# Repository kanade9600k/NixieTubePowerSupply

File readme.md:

# NixieTubePowerSupply

## 概要

* ニキシー管用の高電圧と制御用の電圧を生成する電源回路基板
* デフォルトでは200Vと5Vを生成
* 5Vだけとしても利用可能
* パーツを変えることで他の電圧ようにも流用可

## 回路図

## 外観

* 表

* 裏

## その他

* 高電圧注意
* 一応手元で動きましたが，動作保証はできません

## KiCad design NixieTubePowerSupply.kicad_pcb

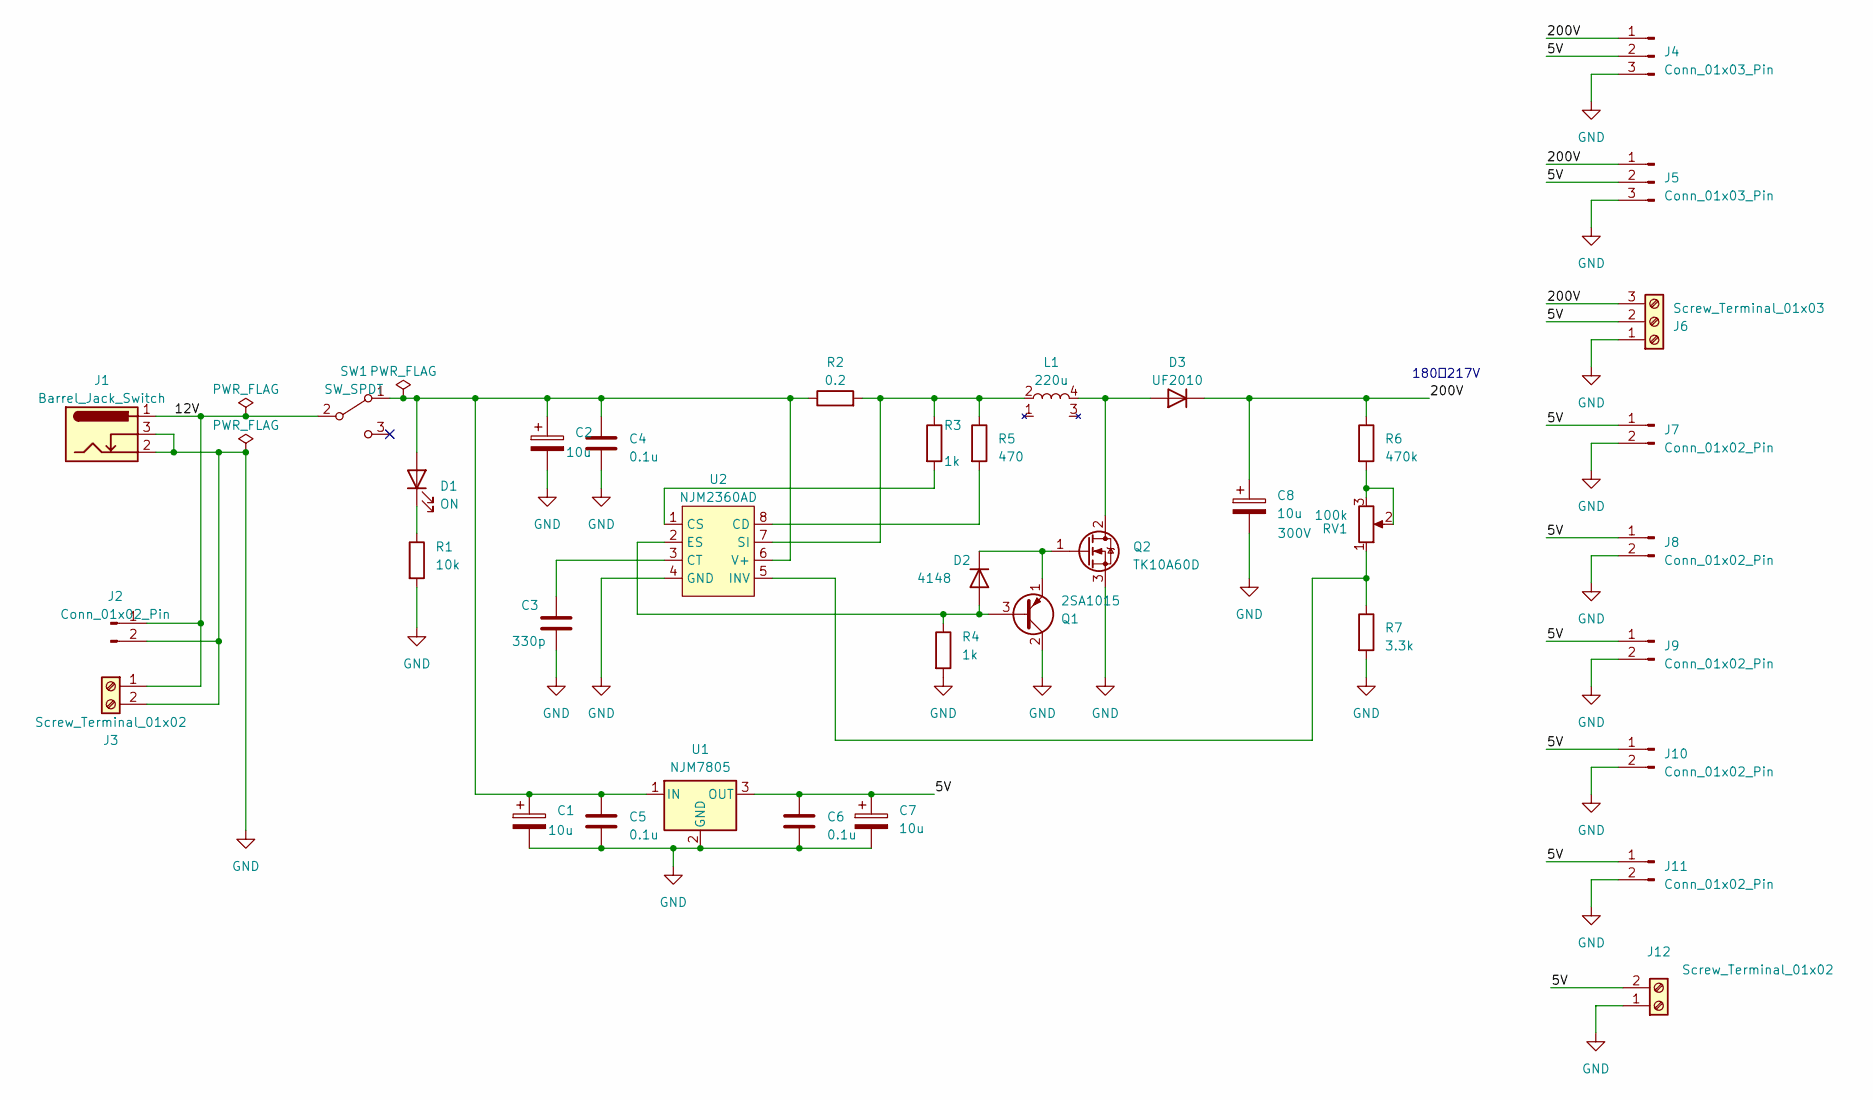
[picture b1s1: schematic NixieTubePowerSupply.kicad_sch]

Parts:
C1, C2, C7: 10u; CP_Radial_D5.0mm_P2.00mm
C3: 330p; C_Disc_D3.0mm_W2.0mm_P2.50mm
C4, C5, C6: 0.1u; C_Disc_D3.0mm_W2.0mm_P2.50mm
C8: 10u; CP_Radial_D10.0mm_P5.00mm
D1: ON; LED_D3.0mm
D2: 4148; D_DO-35_SOD27_P7.62mm_Horizontal
D3: UF2010; D_DO-15_P12.70mm_Horizontal
J1: Barrel_Jack_Switch; BarrelJack_GCT_DCJ200-10-A_Horizontal
J2, J7, J8, J9, J10, J11: Conn_01x02_Pin; JST_XH_B2B-XH-A_1x02_P2.50mm_Vertical
J3, J12: Screw_Terminal_01x02; TerminalBlock_TB111-2-2_P5.08mm
J4, J5: Conn_01x03_Pin; JST_XH_B3B-XH-A_1x03_P2.50mm_Vertical
J6: Screw_Terminal_01x03; TerminalBlock_TB111-2-3_P5.08mm
L1: 220u; RCH-110
Q1: 2SA1015; TO-92_Inline
Q2: TK10A60D; TO-220-3_Horizontal_TabDown
R1: 10k; R_Axial_DIN0207_L6.3mm_D2.5mm_P10.16mm_Horizontal
R2: 0.2; R_Axial_DIN0309_L9.0mm_D3.2mm_P12.70mm_Horizontal
R3, R4: 1k; R_Axial_DIN0207_L6.3mm_D2.5mm_P10.16mm_Horizontal
R5: 470; R_Axial_DIN0207_L6.3mm_D2.5mm_P10.16mm_Horizontal
R6: 470k; R_Axial_DIN0207_L6.3mm_D2.5mm_P10.16mm_Horizontal
R7: 3.3k; R_Axial_DIN0207_L6.3mm_D2.5mm_P10.16mm_Horizontal
RV1: 100k; Potentiometer_GF063P
SW1: SW_SPDT; Switch_Toggle_2MS1-T1-B4-M2-Q-E
U1: NJM7805; TO-220-3_Horizontal_TabDown
U2: NJM2360AD; DIP-8_W7.62mm_Socket

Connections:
/5V: C6.1, C7.1, J4.2, J5.2, J6.2, J7.1, J8.1, J9.1, J10.1, J11.1, J12.2, U1.3 (OUT)
/12V: J1.1, J2.1, J3.1, SW1.2 (B)
/200V: C8.1, D3.1 (K), J4.1, J5.1, J6.3, R6.1
GND: C1.2, C2.2, C3.2, C4.2, C5.2, C6.2, C7.2, C8.2, J1.2, J1.3, J2.2, J3.2, J4.3, J5.3, J6.1, J7.2, J8.2, J9.2, J10.2, J11.2, J12.1, Q1.2 (C), Q2.3 (S), R1.2, R4.2, R7.2, U1.2 (GND), U2.4 (GND)
unnamed: C1.1, C2.1, C4.1, C5.1, D1.2 (A), R2.1, SW1.1 (A), U1.1 (IN), U2.6 (V+)
unnamed: D1.1 (K), R1.1
unnamed: D2.2 (A), Q1.3 (B), R4.1, U2.2 (ES)
unnamed: D2.1 (K), Q1.1 (E), Q2.1 (G)
unnamed: D3.2 (A), L1.4, Q2.2 (D)
unnamed: R6.2, RV1.2, RV1.3
unnamed: R5.2, U2.8 (CD)
unnamed: R3.2, U2.1 (CS)
unnamed: C3.1, U2.3 (CT)
unnamed: R7.1, RV1.1, U2.5 (INV)
unnamed: L1.2, R2.2, R3.1, R5.1, U2.7 (SI)

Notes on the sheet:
180～217V

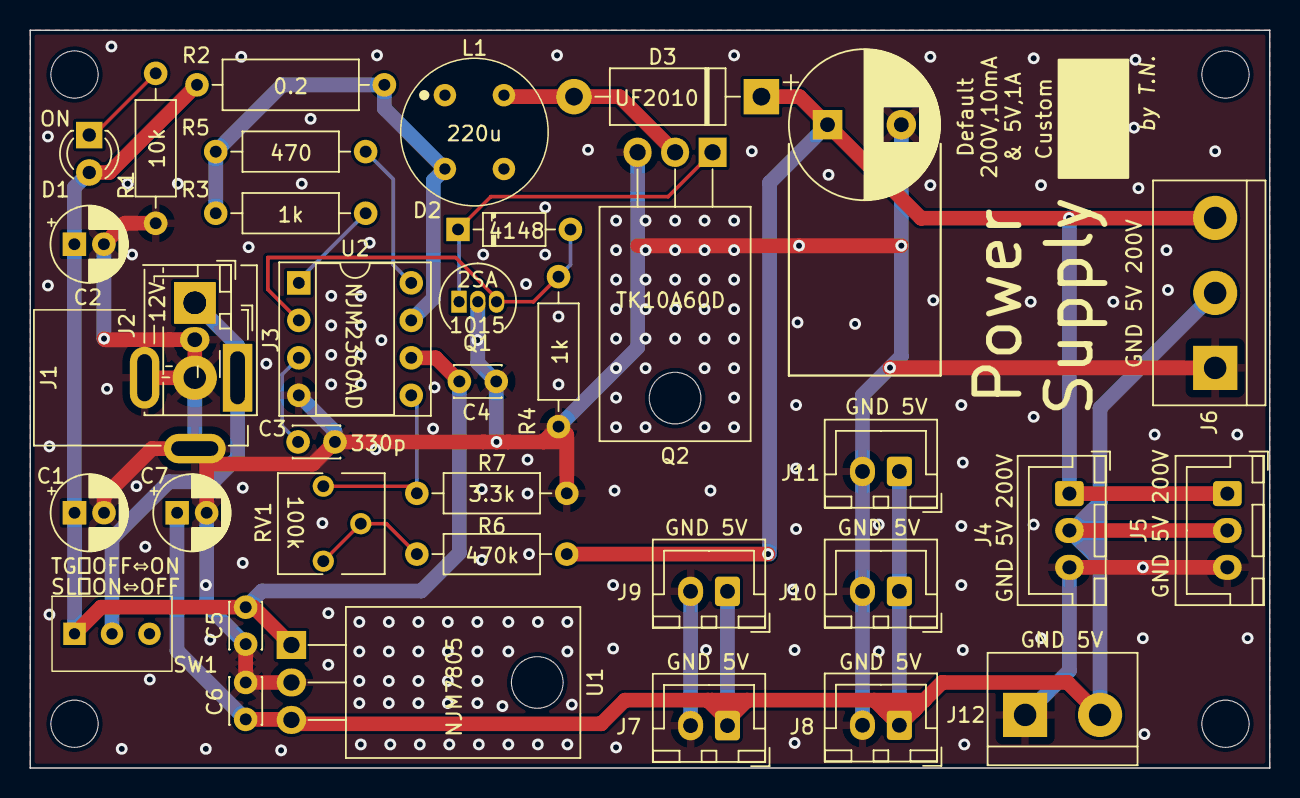
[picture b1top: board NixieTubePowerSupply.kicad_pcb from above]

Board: 2 copper layers, 84.0 x 50.0 mm, 37 parts (0 on the bottom side), 15 nets.

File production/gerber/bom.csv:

Designator,Footprint,Quantity,Value,LCSC Part #
"C1, C2, C7",CP_Radial_D5.0mm_P2.00mm,3,10u,
C3,C_Disc_D3.0mm_W2.0mm_P2.50mm,1,330p,
"C4, C5, C6",C_Disc_D3.0mm_W2.0mm_P2.50mm,3,0.1u,
C8,CP_Radial_D10.0mm_P5.00mm,1,10u,
D1,LED_D3.0mm,1,ON,
D2,D_DO-35_SOD27_P7.62mm_Horizontal,1,4148,
D3,D_DO-15_P12.70mm_Horizontal,1,UF2010,
J1,BarrelJack_GCT_DCJ200-10-A_Horizontal,1,Barrel_Jack_Switch,
"J10, J11, J2, J7, J8, J9",JST_XH_B2B-XH-A_1x02_P2.50mm_Vertical,6,Conn_01x02_Pin,
"J12, J3",TerminalBlock_TB111-2-2_P5.08mm,2,Screw_Terminal_01x02,
"J4, J5",JST_XH_B3B-XH-A_1x03_P2.50mm_Vertical,2,Conn_01x03_Pin,
J6,TerminalBlock_TB111-2-3_P5.08mm,1,Screw_Terminal_01x03,
L1,RCH-110,1,220u,
Q1,TO-92_Inline,1,2SA1015,
Q2,TO-220-3_Horizontal_TabDown,1,TK10A60D,
R1,R_Axial_DIN0207_L6.3mm_D2.5mm_P10.16mm_Horizontal,1,10k,
R2,R_Axial_DIN0309_L9.0mm_D3.2mm_P12.70mm_Horizontal,1,0.2,
"R3, R4",R_Axial_DIN0207_L6.3mm_D2.5mm_P10.16mm_Horizontal,2,1k,
R5,R_Axial_DIN0207_L6.3mm_D2.5mm_P10.16mm_Horizontal,1,470,
R6,R_Axial_DIN0207_L6.3mm_D2.5mm_P10.16mm_Horizontal,1,470k,
R7,R_Axial_DIN0207_L6.3mm_D2.5mm_P10.16mm_Horizontal,1,3.3k,
RV1,Potentiometer_GF063P,1,100k,
SW1,Switch_Toggle_2MS1-T1-B4-M2-Q-E,1,SW_SPDT,
U1,TO-220-3_Horizontal_TabDown,1,NJM7805,
U2,DIP-8_W7.62mm_Socket,1,NJM2360AD,

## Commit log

2023-03-12 最初のコミット
2023-03-16 概略配置を完了
2023-03-16 配置を完了
2023-03-17 配線を完了
2023-03-21 基板サイズを共有のものに変更
2023-05-27 製造後データを追加
2023-05-27 readmeを追加
